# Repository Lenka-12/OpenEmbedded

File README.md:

# OpenEmbedded
## Warm up on UCT dev board 001
- Below is basic functionality
- Microcontroller is send to sleep mode if 60s pass without button press
- Use interrupts for detecting button press
- You may use DMA with timer trigger to read ADCs
### Functionality
| Button Label          |Function                                         |
| ----------------------|-------------------------------------------------|
| SW0 press             | Read POT1 and POT2 and the display values on LCD|
| SW1 press             | Read temperature sensor and display value on LCD|
| SW2 press             | Toggles LED0-LED4 every 1s                      |
| SW3 press             | Wake up microcontroller from deep sleep         |

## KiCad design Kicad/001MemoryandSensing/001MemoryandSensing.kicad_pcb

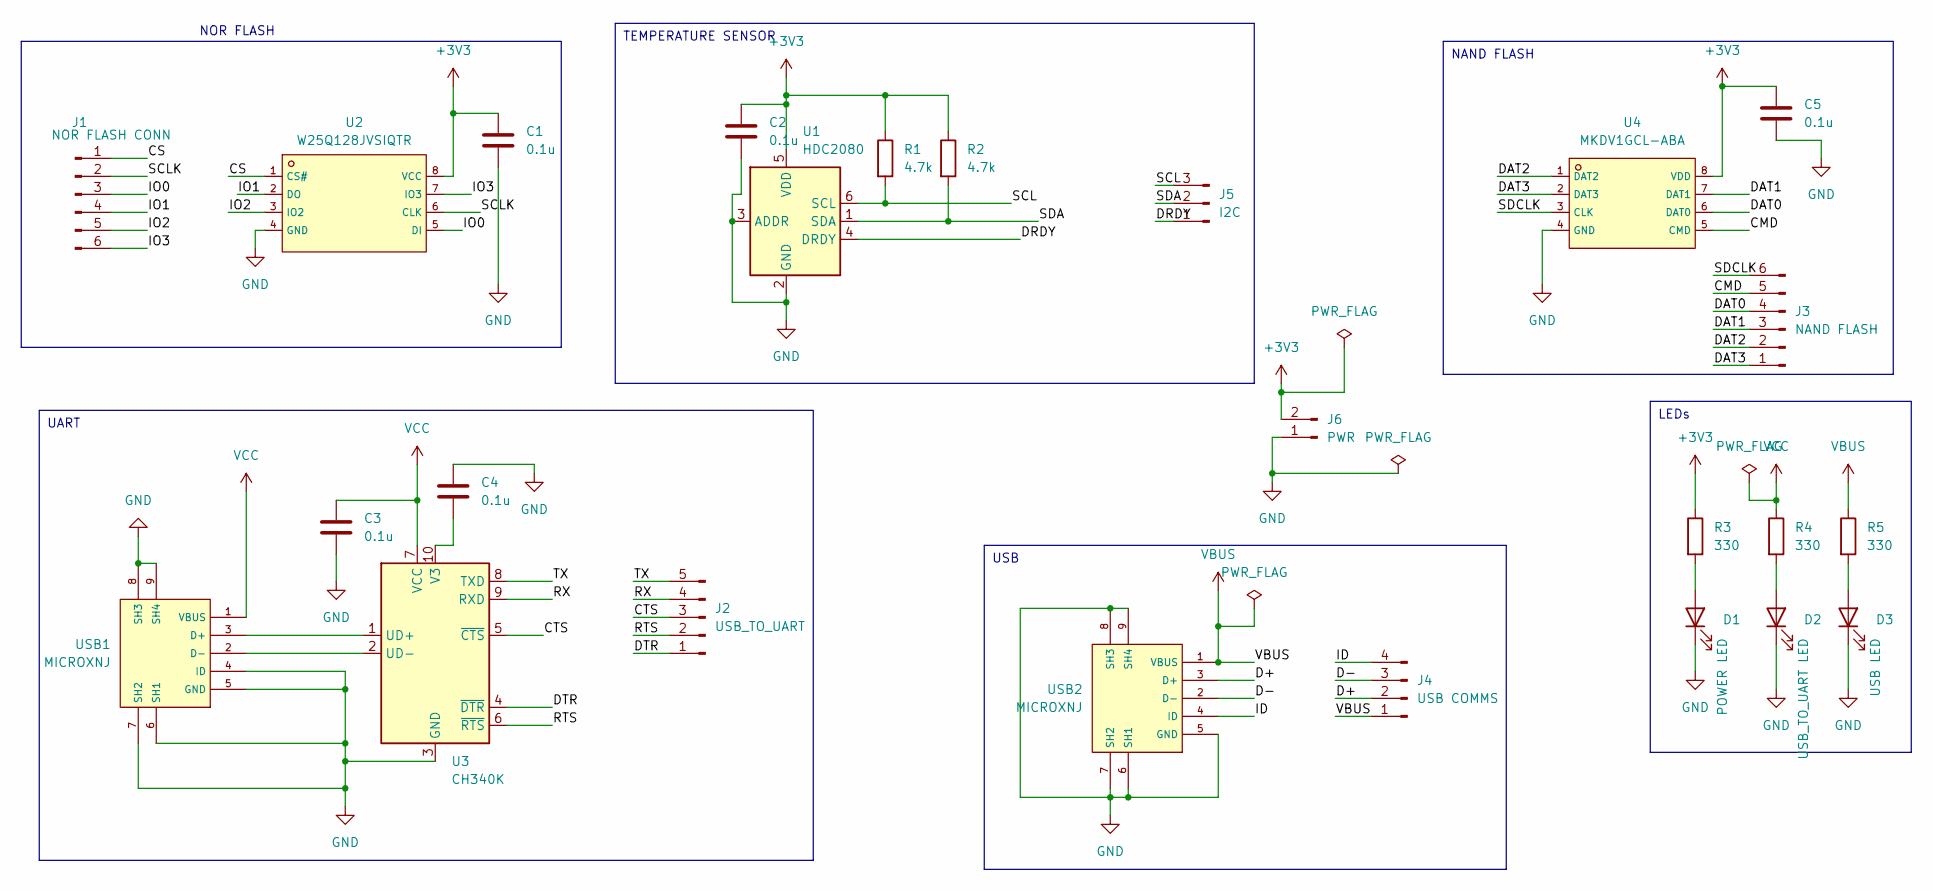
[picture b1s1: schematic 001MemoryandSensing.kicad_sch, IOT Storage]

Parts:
C1, C2, C3, C4, C5: 0.1u; C_0805_2012Metric
D1: POWER LED; LED_1206_3216Metric
D2: USB_TO_UART LED; LED_1206_3216Metric
D3: USB LED; LED_1206_3216Metric
J1: NOR FLASH CONN; PinHeader_1x06_P2.54mm_Vertical
J2: USB_TO_UART; PinHeader_1x05_P2.54mm_Vertical
J3: NAND FLASH; PinHeader_1x06_P2.54mm_Vertical
J4: USB COMMS; PinHeader_1x04_P2.54mm_Vertical
J5: I2C; PinHeader_1x03_P2.54mm_Vertical
J6: PWR; PinHeader_1x02_P2.54mm_Vertical
R1, R2: 4.7k; R_0805_2012Metric
R3, R4, R5: 330; R_0805_2012Metric
U1: HDC2080; Texas_PWSON-N6
U2: W25Q128JVSIQTR; SOIC-8_L5.3-W5.3-P1.27-LS8.0-BL; LCSC C97521
U3: CH340K; SSOP-10-1EP_3.9x4.9mm_P1mm_EP2.1x3.3mm
U4: MKDV1GCL-ABA; LGA-8_L6.0-W8.0-P1.27-TL; LCSC C6152616
USB1, USB2: MICROXNJ; MICRO-USB-SMD_MICROXNJ; LCSC C404969

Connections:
+3V3: C1.1, C2.1, C5.1, J6.2, R1.1, R2.1, R3.1, U1.5 (VDD), U2.8 (VCC), U4.8 (VDD)
/CMD: J3.5, U4.5 (CMD)
/CS: J1.1, U2.1 (CS#)
/CTS: J2.3, U3.5 (~CTS)
/D+: J4.2, USB2.3 (D+)
/D-: J4.3, USB2.2 (D-)
/DAT0: J3.4, U4.6 (DAT0)
/DAT1: J3.3, U4.7 (DAT1)
/DAT2: J3.2, U4.1 (DAT2)
/DAT3: J3.1, U4.2 (DAT3)
/DRDY: J5.1, U1.4 (DRDY)
/DTR: J2.1, U3.4 (~DTR)
/ID: J4.4, USB2.4 (ID)
/IO0: J1.3, U2.5 (DI)
/IO1: J1.4, U2.2 (DO)
/IO2: J1.5, U2.3 (IO2)
/IO3: J1.6, U2.7 (IO3)
/RTS: J2.2, U3.6 (~RTS)
/RX: J2.4, U3.9 (RXD)
/SCL: J5.3, R1.2, U1.6 (SCL)
/SCLK: J1.2, U2.6 (CLK)
/SDA: J5.2, R2.2, U1.1 (SDA)
/SDCLK: J3.6, U4.3 (CLK)
/TX: J2.5, U3.8 (TXD)
GND: C1.2, C2.2, C3.2, C4.1, C5.2, D1.1 (K), D2.1 (K), D3.1 (K), J6.1, U1.2 (GND), U1.3 (ADDR), U2.4 (GND), U3.3 (GND), U3.11 (GND), U4.4 (GND), USB1.4 (ID), USB1.5 (GND), USB1.6 (SH1), USB1.7 (SH2), USB1.8 (SH3), USB1.9 (SH4), USB2.5 (GND), USB2.6 (SH1), USB2.7 (SH2), USB2.8 (SH3), USB2.9 (SH4)
unnamed: D1.2 (A), R3.2
unnamed: D2.2 (A), R4.2
unnamed: D3.2 (A), R5.2
unnamed: U3.1 (UD+), USB1.3 (D+)
unnamed: U3.2 (UD-), USB1.2 (D-)
unnamed: C4.2, U3.10 (V3)
VBUS: J4.1, R5.1, USB2.1 (VBUS)
VCC: C3.1, R4.1, U3.7 (VCC), USB1.1 (VBUS)

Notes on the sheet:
LEDs
USB
UART
TEMPERATURE SENSOR
NAND FLASH
NOR FLASH

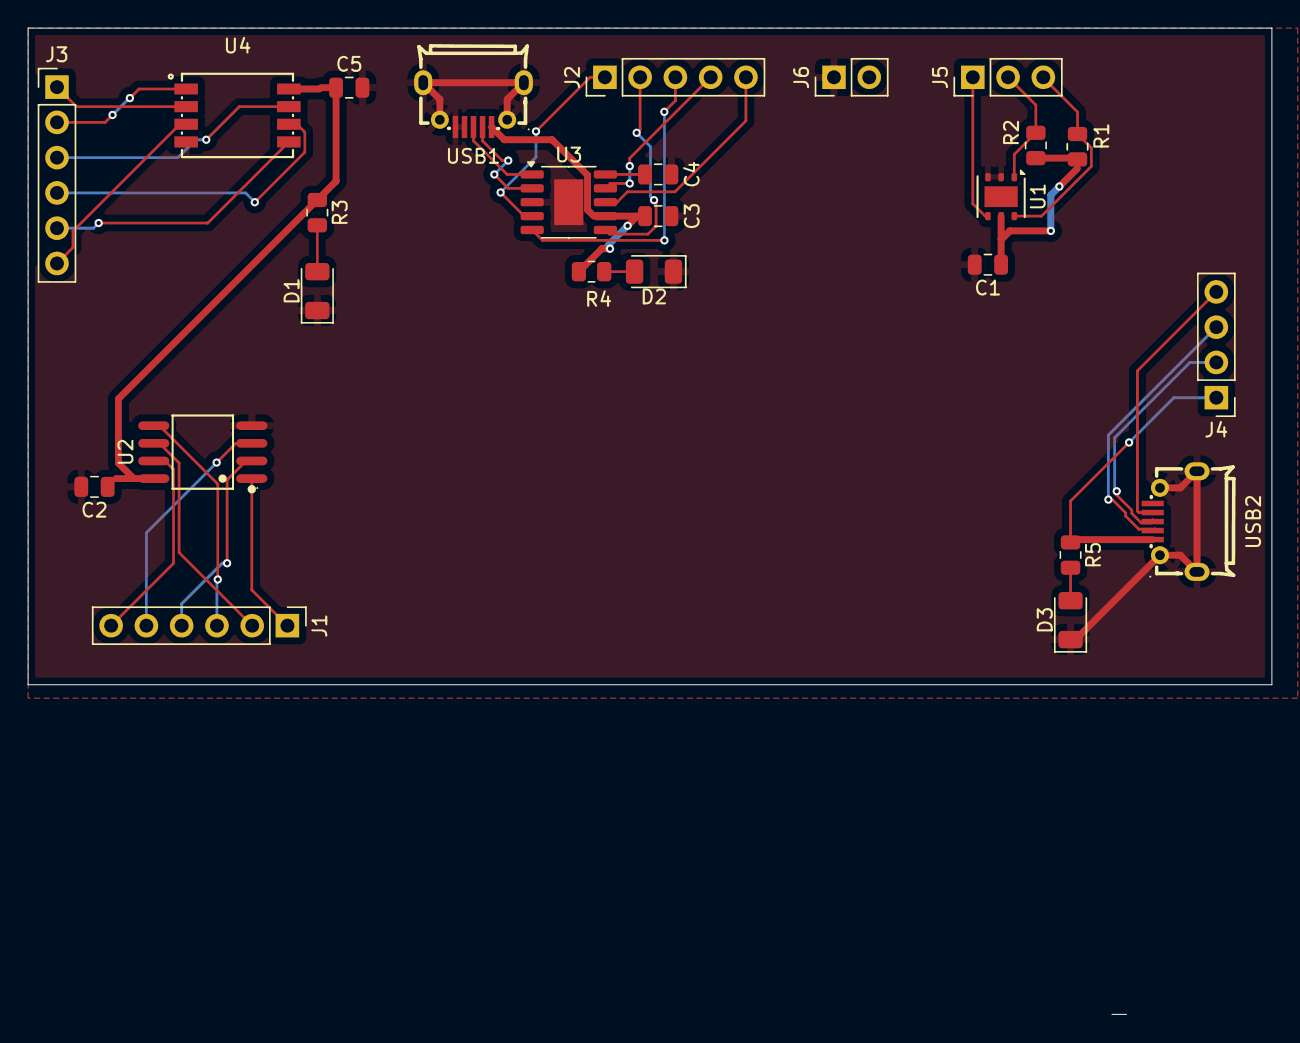
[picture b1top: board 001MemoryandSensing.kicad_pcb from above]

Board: 2 copper layers, 89.6 x 71.0 mm, 25 parts (0 on the bottom side), 33 nets.

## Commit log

2024-05-28 first project instructions
2024-06-09 I2C EEPROM and RTC libraries
2024-06-09 HTS221 and STTS751 libraries
2024-06-09 stm32f4 pll configuration in asm
